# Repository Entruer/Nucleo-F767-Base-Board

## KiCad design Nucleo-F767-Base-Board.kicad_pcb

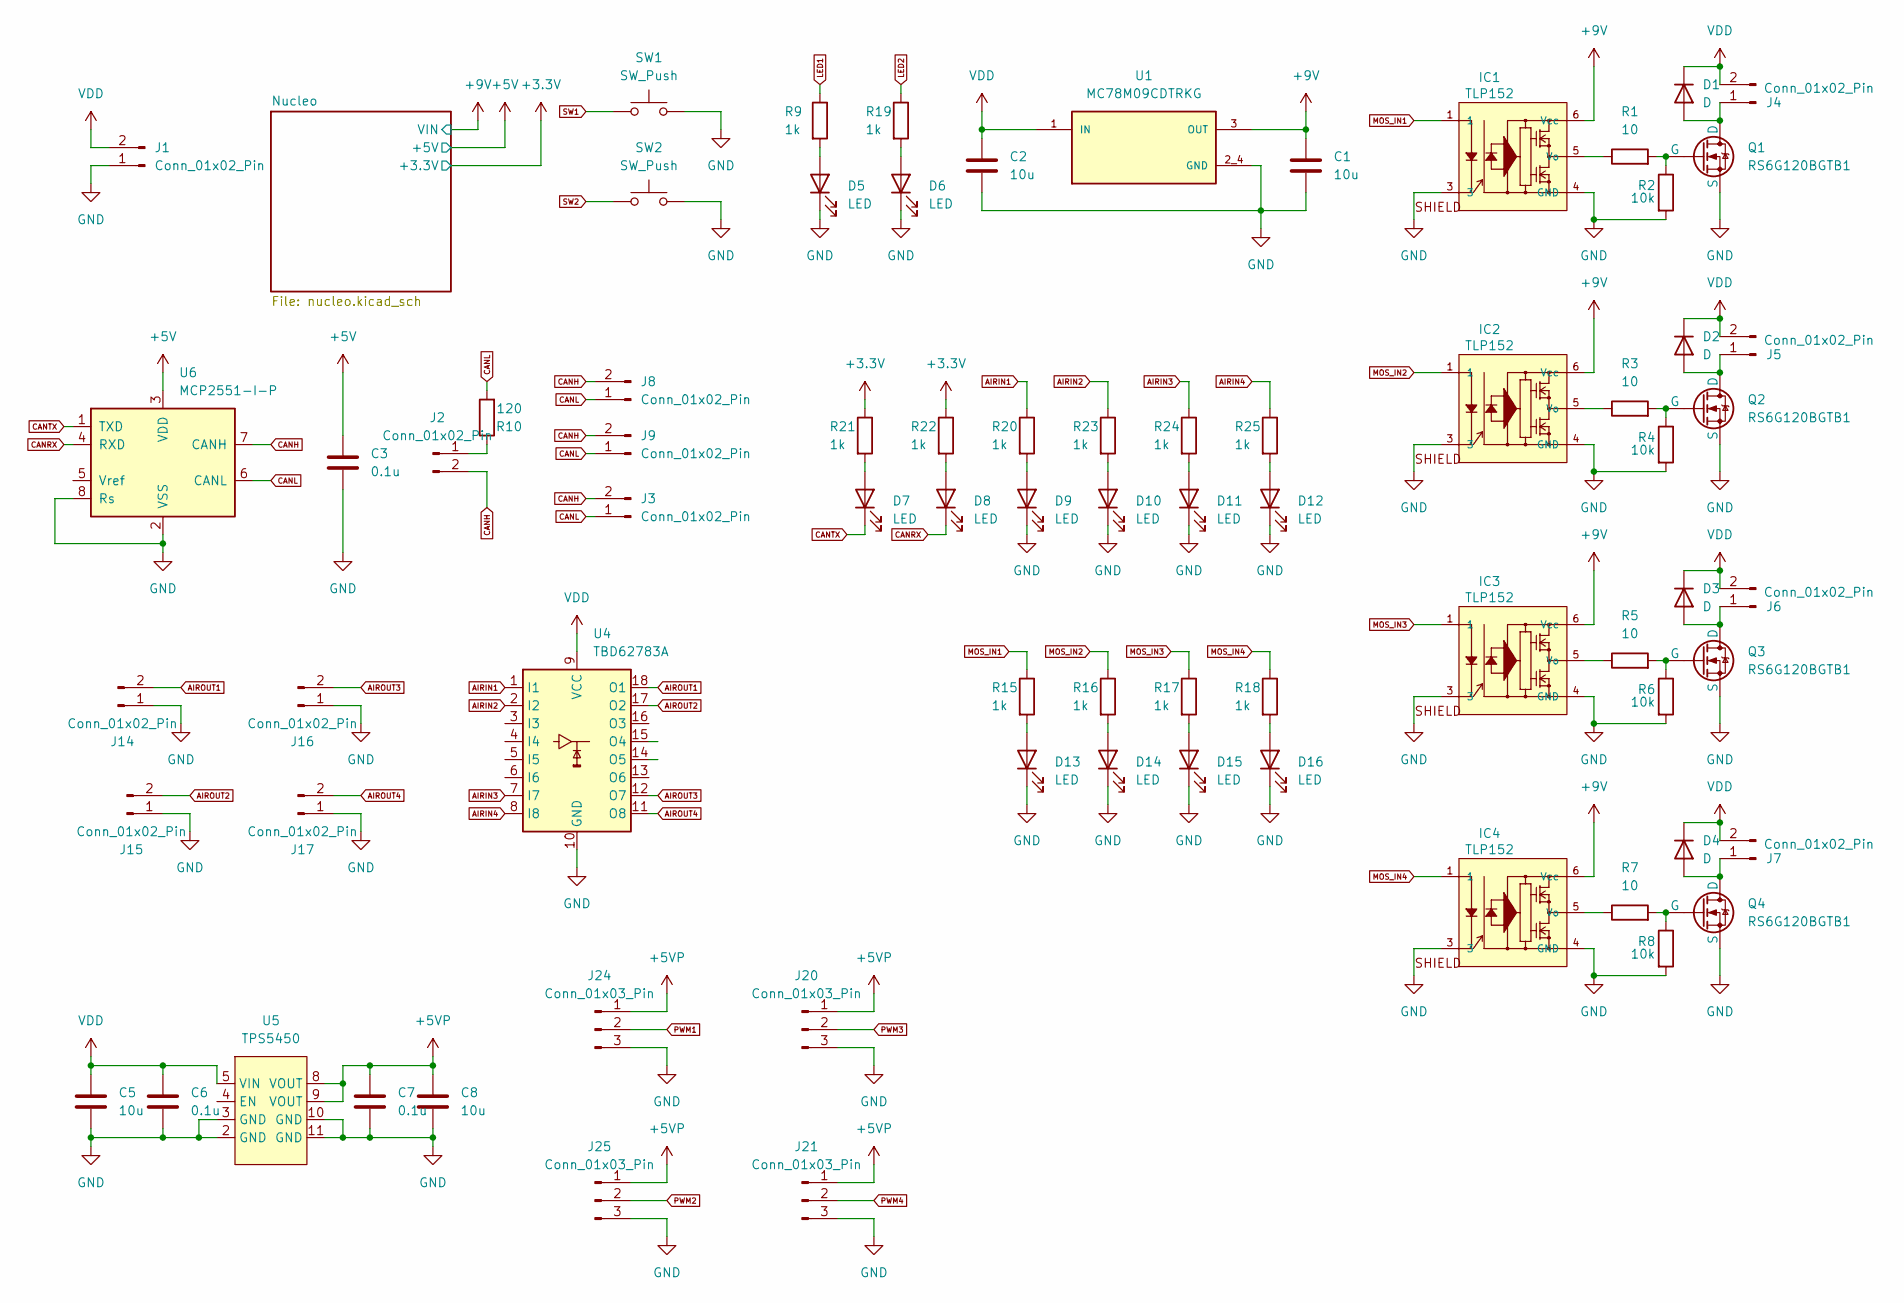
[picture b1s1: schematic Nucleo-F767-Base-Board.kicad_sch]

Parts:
C1, C2, C5, C8: 10u; C_0603_1608Metric
C3, C6, C7: 0.1u; C_0603_1608Metric
D1, D2, D3, D4: D; PDS54013
D5, D6, D7, D8, D9, D10, D11, D12, D13, D14, D15, D16: LED; LED_0603_1608Metric
IC1, IC2, IC3, IC4: TLP152; 5PIN_SO6_TOS; MANUFACTURER_PART_NUMBER TLP152
J1: Conn_01x02_Pin; AMASS_XT60PW-M_1x02_P7.20mm_Horizontal
J2: Conn_01x02_Pin; PinHeader_1x02_P2.54mm_Vertical
J3, J8, J9: Conn_01x02_Pin; JST_XA_B02B-XASK-1_1x02_P2.50mm_Vertical
J4, J5, J6, J7: Conn_01x02_Pin; AMASS_XT30PW-F_1x02_P2.50mm_Horizontal
J14, J15, J16, J17: Conn_01x02_Pin; JST_XA_S02B-XASK-1_1x02_P2.50mm_Horizontal
J20, J21: Conn_01x03_Pin; JST_XA_B03B-XASK-1_1x03_P2.50mm_Vertical
J24, J25: Conn_01x03_Pin; JST_XA_S03B-XASK-1_1x03_P2.50mm_Horizontal
Q1, Q2, Q3, Q4: RS6G120BGTB1; DPAK127P_600X120-5N
R1, R3, R5, R7: 10; R_0603_1608Metric
R2, R4, R6, R8: 10k; R_0603_1608Metric
R9, R15, R16, R17, R18, R19, R20, R21, R22, R23, R24, R25: 1k; R_0603_1608Metric
R10: 120; R_0603_1608Metric
SW1, SW2: SW_Push; SW_PUSH_6mm
U1: MC78M09CDTRKG; VREG_MC78M09CDTRKG; PARTREV 29
U4: TBD62783A; SOIC-18W_7.5x11.6mm_P1.27mm
U5: TPS5450; TPS5450-module
U6: MCP2551-I-P; DIP-8_W7.62mm

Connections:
+3.3V: R21.1, R22.1; also elsewhere on the board
+5V: C3.1, U6.3 (VDD); also elsewhere on the board
+5VP: C7.1, C8.1, J20.1, J21.1, J24.1, J25.1, U5.8 (VOUT), U5.9 (VOUT)
+9V: C1.1, IC1.6 (Vcc), IC2.6 (Vcc), IC3.6 (Vcc), IC4.6 (Vcc), U1.3 (OUT); also elsewhere on the board
AIRIN1: R20.1, U4.1 (I1); also elsewhere on the board
AIRIN2: R23.1, U4.2 (I2); also elsewhere on the board
AIRIN3: R24.1, U4.7 (I7); also elsewhere on the board
AIRIN4: R25.1, U4.8 (I8); also elsewhere on the board
AIROUT1: J14.2, U4.18 (O1)
AIROUT2: J15.2, U4.17 (O2)
AIROUT3: J16.2, U4.12 (O7)
AIROUT4: J17.2, U4.11 (O8)
CANH: J2.2, J3.2, J8.2, J9.2, U6.7 (CANH)
CANL: J3.1, J8.1, J9.1, R10.2, U6.6 (CANL)
CANRX: D8.1 (K), U6.4 (RXD); also elsewhere on the board
CANTX: D7.1 (K), U6.1 (TXD); also elsewhere on the board
GND: C1.2, C2.2, C3.2, C5.2, C6.2, C7.2, C8.2, D5.1 (K), D6.1 (K), D9.1 (K), D10.1 (K), D11.1 (K), D12.1 (K), D13.1 (K), D14.1 (K), D15.1 (K), D16.1 (K), IC1.3, IC1.4 (GND), IC2.3, IC2.4 (GND), IC3.3, IC3.4 (GND), IC4.3, IC4.4 (GND), J1.1, J14.1, J15.1, J16.1, J17.1, J20.3, J21.3, J24.3, J25.3, Q1.3 (S), Q2.3 (S), Q3.3 (S), Q4.3 (S), R2.2, R4.2, R6.2, R8.2, SW1.2, SW2.2, U1.2_4 (GND), U4.10 (GND), U5.2 (GND), U5.3 (GND), U5.10 (GND), U5.11 (GND), U6.2 (VSS), U6.8 (Rs); also elsewhere on the board
LED1: R9.1; also elsewhere on the board
LED2: R19.1; also elsewhere on the board
MOS_IN1: IC1.1, R15.1; also elsewhere on the board
MOS_IN2: IC2.1, R16.1; also elsewhere on the board
MOS_IN3: IC3.1, R17.1; also elsewhere on the board
MOS_IN4: IC4.1, R18.1; also elsewhere on the board
unnamed: D1.2 (A), J4.1, Q1.1 (D)
unnamed: D2.2 (A), J5.1, Q2.1 (D)
unnamed: D3.2 (A), J6.1, Q3.1 (D)
unnamed: D4.2 (A), J7.1, Q4.1 (D)
unnamed: D5.2 (A), R9.2
unnamed: D6.2 (A), R19.2
unnamed: D7.2 (A), R21.2
unnamed: D8.2 (A), R22.2
unnamed: D9.2 (A), R20.2
unnamed: D10.2 (A), R23.2
unnamed: D11.2 (A), R24.2
unnamed: D12.2 (A), R25.2
unnamed: D13.2 (A), R15.2
unnamed: D14.2 (A), R16.2
unnamed: D15.2 (A), R17.2
unnamed: D16.2 (A), R18.2
unnamed: IC1.5 (Vo), R1.1
unnamed: IC2.5 (Vo), R3.1
unnamed: IC3.5 (Vo), R5.1
unnamed: IC4.5 (Vo), R7.1
unnamed: J2.1, R10.1
unnamed: Q1.2 (G), R1.2, R2.1
unnamed: Q2.2 (G), R3.2, R4.1
unnamed: Q3.2 (G), R5.2, R6.1
unnamed: Q4.2 (G), R7.2, R8.1
PWM1: J24.2; also elsewhere on the board
PWM2: J25.2; also elsewhere on the board
PWM3: J20.2; also elsewhere on the board
PWM4: J21.2; also elsewhere on the board
SW1: SW1.1; also elsewhere on the board
SW2: SW2.1; also elsewhere on the board
VDD: C2.1, C5.1, C6.1, D1.1 (K), D2.1 (K), D3.1 (K), D4.1 (K), J1.2, J4.2, J5.2, J6.2, J7.2, U1.1 (IN), U4.9 (VCC), U5.5 (VIN)

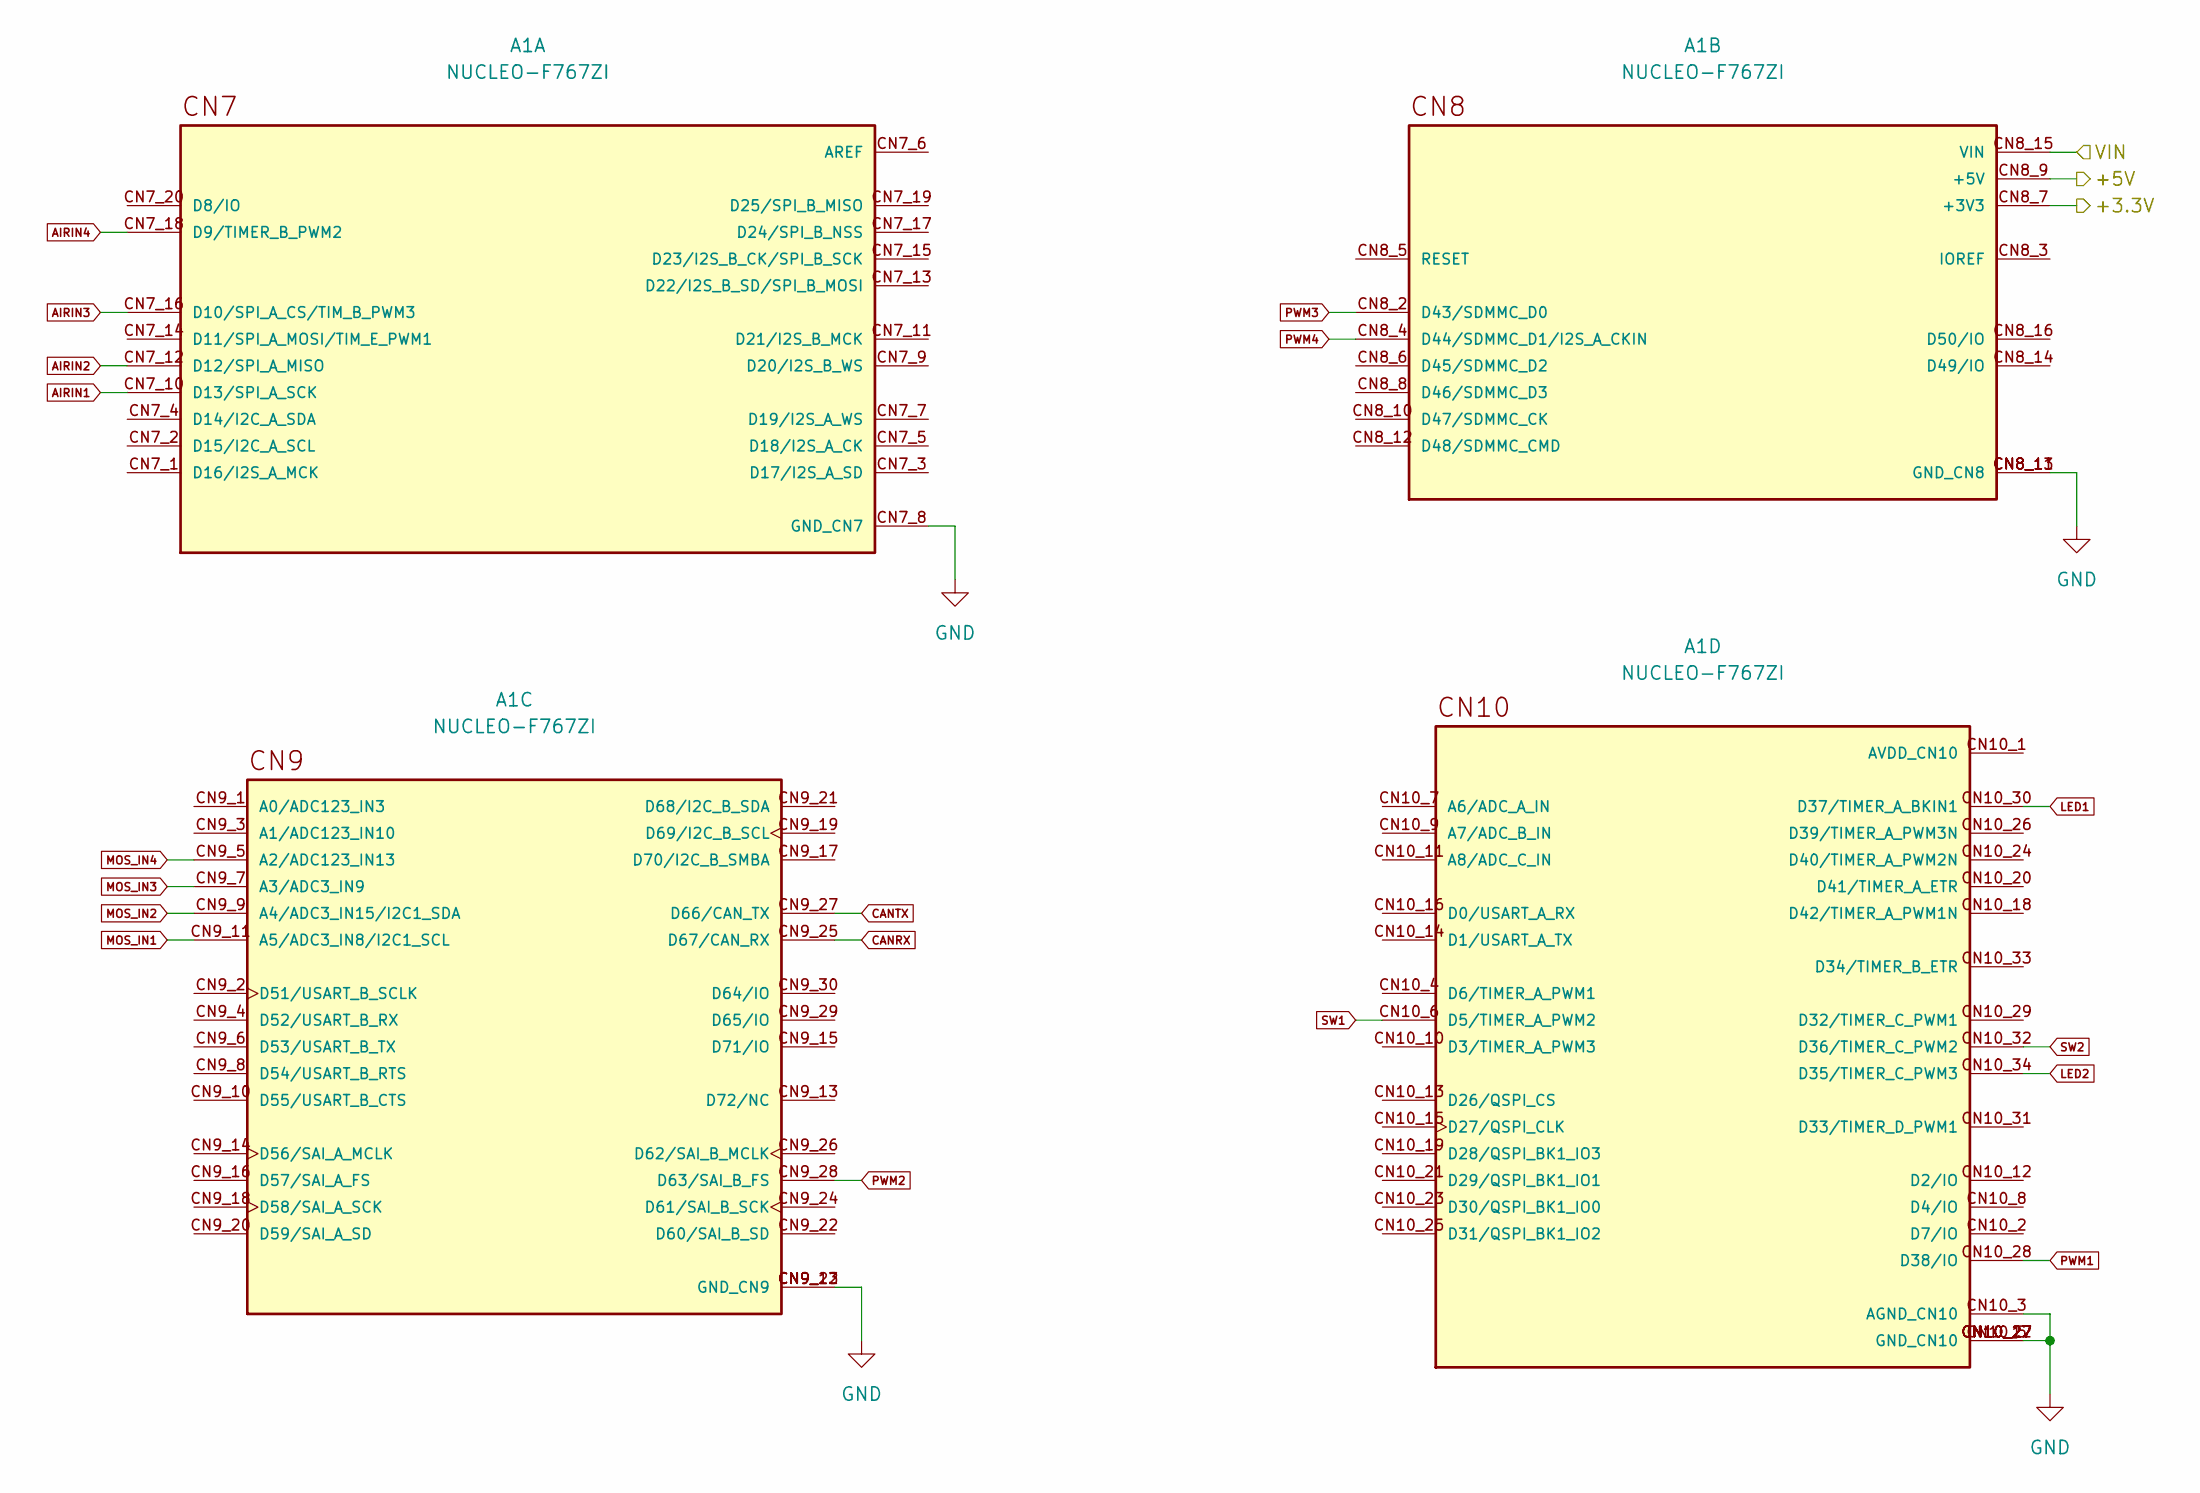
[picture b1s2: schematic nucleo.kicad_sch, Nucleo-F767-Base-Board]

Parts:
A1: NUCLEO-F767ZI; ST_NUCLEO-F767ZI

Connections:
+3.3V: A1.CN8_7 (+3V3); also elsewhere on the board
+5V: A1.CN8_9 (+5V); also elsewhere on the board
+9V: A1.CN8_15 (VIN); also elsewhere on the board
AIRIN1: A1.CN7_10 (D13/SPI_A_SCK); also elsewhere on the board
AIRIN2: A1.CN7_12 (D12/SPI_A_MISO); also elsewhere on the board
AIRIN3: A1.CN7_16 (D10/SPI_A_CS/TIM_B_PWM3); also elsewhere on the board
AIRIN4: A1.CN7_18 (D9/TIMER_B_PWM2); also elsewhere on the board
CANRX: A1.CN9_25 (D67/CAN_RX); also elsewhere on the board
CANTX: A1.CN9_27 (D66/CAN_TX); also elsewhere on the board
GND: A1.CN7_8 (GND_CN7), A1.CN8_11 (GND_CN8), A1.CN8_13 (GND_CN8), A1.CN9_12 (GND_CN9), A1.CN9_23 (GND_CN9), A1.CN10_3 (AGND_CN10), A1.CN10_5 (GND_CN10), A1.CN10_17 (GND_CN10), A1.CN10_22 (GND_CN10), A1.CN10_27 (GND_CN10); also elsewhere on the board
LED1: A1.CN10_30 (D37/TIMER_A_BKIN1); also elsewhere on the board
LED2: A1.CN10_34 (D35/TIMER_C_PWM3); also elsewhere on the board
MOS_IN1: A1.CN9_11 (A5/ADC3_IN8/I2C1_SCL); also elsewhere on the board
MOS_IN2: A1.CN9_9 (A4/ADC3_IN15/I2C1_SDA); also elsewhere on the board
MOS_IN3: A1.CN9_7 (A3/ADC3_IN9); also elsewhere on the board
MOS_IN4: A1.CN9_5 (A2/ADC123_IN13); also elsewhere on the board
PWM1: A1.CN10_28 (D38/IO); also elsewhere on the board
PWM2: A1.CN9_28 (D63/SAI_B_FS); also elsewhere on the board
PWM3: A1.CN8_2 (D43/SDMMC_D0); also elsewhere on the board
PWM4: A1.CN8_4 (D44/SDMMC_D1/I2S_A_CKIN); also elsewhere on the board
SW1: A1.CN10_6 (D5/TIMER_A_PWM2); also elsewhere on the board
SW2: A1.CN10_32 (D36/TIMER_C_PWM2); also elsewhere on the board

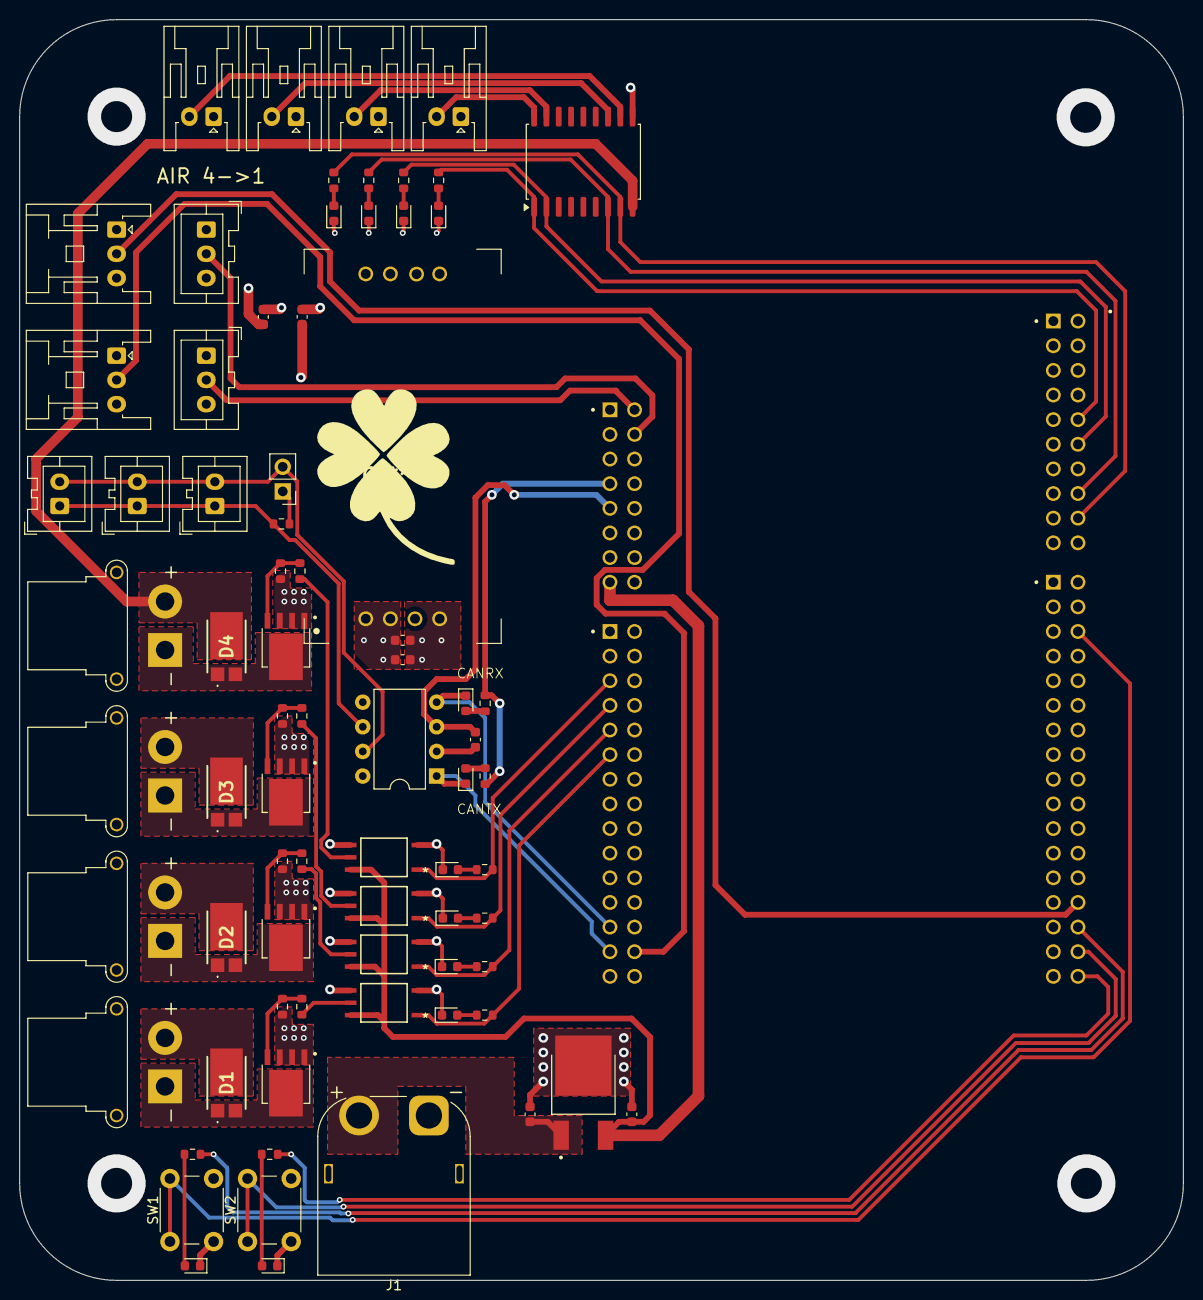
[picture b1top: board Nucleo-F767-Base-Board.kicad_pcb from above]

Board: 2 copper layers, 120.0 x 130.0 mm, 76 parts (0 on the bottom side), 55 nets.

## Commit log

2024-07-31 Finish 1.0
2024-07-31 fix gitignore.
2024-08-01 Change pin.
2024-08-19 Update.
2024-08-19 Fixed

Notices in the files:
parts and their libraries:
COPYRIGHT: Copyright (C) 2022 Ultra Librarian. All rights reserved.
